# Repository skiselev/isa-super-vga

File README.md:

# isa-super-vga
Trident TVGA9000i based Super VGA board

## Introduction

The ISA Super VGA card is based on the Trident TVGA9000i Super VGA controller IC. It offers excellent compatibility with the original IBM VGA, as well as a good emulation of older CGA, EGA, Hercules and MDA adapters. The ISA Super VGA card was designed to be used with the [Xi 8088 Processor Board](https://github.com/skiselev/xi_8088), but it also works in IBM PC/XT and their clones. It will work in 16-bit ISA slots of AT-compatible computers, but its performance will be inferior to 16-bit VGA cards.

Note: PCB Version 1.0 requires a rework for compatibility with the original IBM PC and IBM XT computers, please see the Errata section below. This errata was fixed in the PCB Version 1.1

## Specifications

* Supports 256 KiB or 512 KiB video memory using two or four 256 Kbit x 4 DRAM ICs.
* 8088-friendly VGA BIOS.
* Only 6 ICs (SVGA IC, BIOS, four DRAM chips), some capacitors, resistors and inductors.

## Hardware Documentation

### Schematic and PCB Layout

[Schematic - Version 1.1](KiCad/ISA_SVGA-Schematic-1.1.pdf)

[PCB Layout - Version 1.1](KiCad/ISA_SVGA-Board-1.1.pdf)

### Bill of Materials

Component Type     | Reference | Description                                               | Quantity | Possible sources and notes
------------------ | --------- | --------------------------------------------------------- | -------- | --------------------------
PCB                |           | ISA Super VGA PCB                                         | 1        | Refer to the [RetroBrew Computers Board Inventory page](https://retrobrewcomputers.org/doku.php?id=boardinventory) for ordering information, or order from a PCB manufacturer of your choice using provided Gerber or KiCad files. Here is [OSH Park project link](https://oshpark.com/shared_projects/M9jRwsu1).
Integrated Circuit | U1        | Trident TVGA9000i-3                                       | 1        | Utsource or other component dealers. Other TVGA9000i versions can be used (e.g. TVGA9000i-1)
Integrated Circuit | U2        | 27C256 UV erasable EPROM or OTP ROM                       | 1        | Unicorn Electronics, Jameco, Mouser (OTP ROM)
Integrated Circuit | U3 - U6   | Micron MT4C4256, Motorola MCM514256, or similar 256 Kbit x 4 DRAM, 70ns or less | 2 or 4 | Unicorn Electronics. Install 4 for the total memory of 512 KiB or two for 256 KiB.
Capacitor          | C1 - C12  | 0.1 uF ceramic, 5.08 mm pitch                             | 12       | Mouser 810-FG28X7R1H104KNT0 
Capacitor          | C13 - C16 | 10 uF, 16V, multilayer ceramic or tantalum, 5.08 mm pitch | 4        | Mouser 810-FG26X7R1E106KRT0 
Capacitor          | C17       | 1 nF ceramic, 5.08 mm pitch                               | 1        | Mouser 810-FG28C0G2A102JNT6
Capacitor          | C18       | 470 pF ceramic, 5.08 mm pitch                             | 1        | Mouser 810-FG28C0G1H471JNT0 
Capacitor          | C19       | 100 pF ceramic, 5.08 mm pitch                             | 1        | Mouser 810-FG28C0G1H101JNT0 
Capacitor          | C20 - C27 | 47 pF ceramic, 5.08 mm pitch                              | 8        | Mouser 810-FG28C0G1H470JNT0
Resistor           | R1 - R8   | 4.7 k, 1/4 W                                              | 8        | Mouser 291-4.7K-RC
Resistor           | R9        | 1 k, 1/4 W                                                | 1        | Mouser 291-1K-RC
Resistor           | R10 - R13 | 150 Ohm, 1/4 W                                            | 4        | Mouser 291-150-RC
Resistor           | R14       | 100 Ohm, 1/4 W                                            | 1        | Mouser 291-100-RC
Resistor           | R15, R16  | 33 Ohm, 1/4 W                                             | 2        | Mouser 291-33-RC
Connector          | P1        | DE15F, right angle PCB mount                              | 1        | Mouser 806-K66X-E15S-NJVESA, 571-1-1734344-1 (blue color), 806-K66X-E15S-NJ30
Connector          | JP1       | 2 pin header                                              | 1        | Mouser 649-68002-102HLF
Inductor           | L1, L3    | 5.7 uH                                                    | 2        | Mouser 542-78F5R6J-RC
Inductor           | L2        | 2.7 uH                                                    | 1        | Mouser 542-78F2R7-RC
Filter             | FB1 - FB6 | EMI Filter Bead                                           | 6        | Mouser 623-2743001112LF
Crystal            | X1        | 40 MHz                                                    | 1        | Mouser 815-ABL-40-B2
Crystal Insulator  | X1        | Bivar CI-192-028-SR                                       | 1        | Mouser 749-CI-192-028-SR, optional, to prevent crystal from shortcircuiting the traces underneath it.
IC Socket          | U2        | 28 pin 600 mil (wide) DIP socket                          | 1        | Mouser 517-4828-6000-CP
IC Socket          | U3 - U6   | 20 pin 300 mil (narrow) DIP socket                        | 4        | Mouser 517-4820-3000-CP
Bracket            |           | ISA card bracket - Keystone 9200-1                        | 1        | Mouser 534-9200-1, or a [3D printed bracket](https://www.thingiverse.com/thing:6473572)

### Construction Notes

#### Display Type Detection

* TVGA9000i VGA controller uses VGA connector pin 12 as **MONITOR** signal to detect the of type of the display. Older, pre-[DDC](https://en.wikipedia.org/wiki/Display_Data_Channel) displays made approximately until 1995, have that signal either unconnected - for color monitors, or grounded - for monochrome monitors. Newer displays use that signal as the DDC/SDA signal. Unfortunately, it can result in TVGA9000i incorrectly detecting the monitor as monochrome. If you're not planning to use monochrome monitor, you can skip FB6 and C17 components. In this case R6 will be pulling the MONITOR signal up, and TVGA9000i will detect the display as a color one.

## Changes

### Version 1.1

* Fix ALE errata. ALE signal is now connected to 5V
* Slightly move VGA DE-9F connector (about 1.27 mm up and 0.8 mm back) to better comply with ISA card size and bracket placement specifications

### Version 1.0

* Minor board modifications around JP1

## Errata

### Version 1.1
* C17 is incorrectly marked as 1 uF on the silkscreen. The correct value is 1 nF, as shown in the BoM. Also see **Display Type Detection** note above.

### Version 1.0

* The original IBM PC, the original IBM XT, and XT clones that closely follow IBM XT schematic do not implement the ALE signal properly. In these computers the ALE signal occasionally activated during DMA cycles, for example during memory refresh, while the address on the address bus is invalid. This confuses the Trident TVGA controller. The following rework is required to make ISA Super VGA work in these computers: The TVGA9000 ALE signal needs to be disconnected from the ISA ALE signal, and connected to the 5V power signal. The photo below shows such modification (photo credit: [keropi](https://forum.vcfed.org/index.php?members/keropi.23086/) at [VCFed forum](https://forum.vcfed.org/index.php)).

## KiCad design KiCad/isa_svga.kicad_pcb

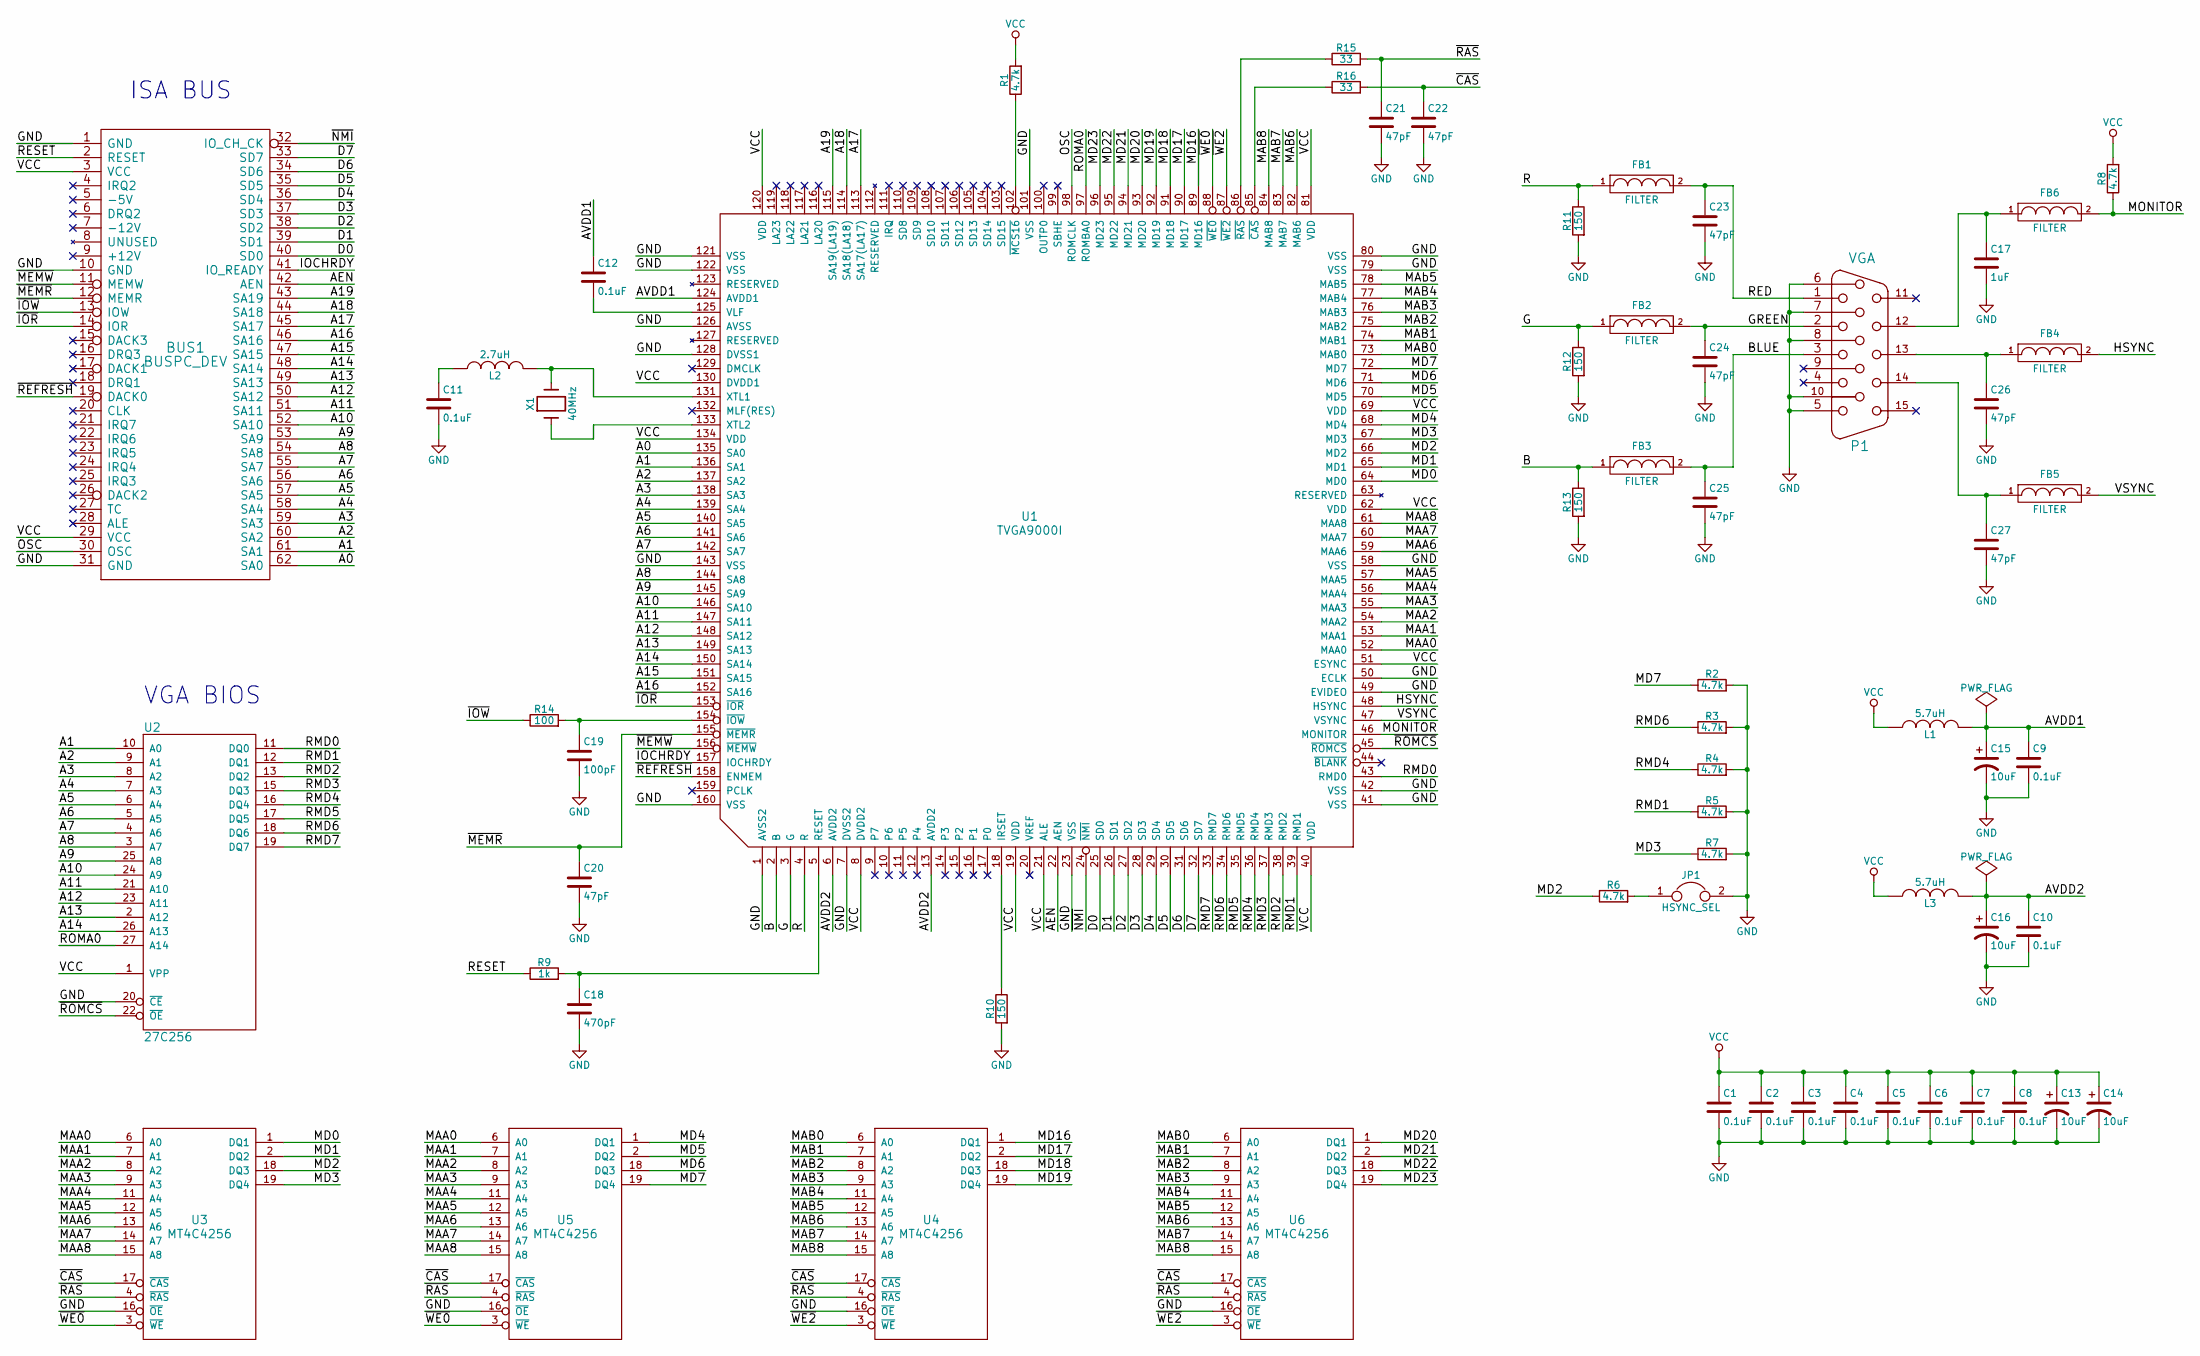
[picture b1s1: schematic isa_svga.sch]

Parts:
BUS1: BUSPC_DEV; Conn_Edge_ISA8
C1, C2, C3, C4, C5, C6, C7, C8, C9, C10, C11, C12: 0.1uF; Cap_Cer_508
C13, C14, C15, C16: 10uF; Cap_Tant_508
C17: 1uF; Cap_Cer_508
C18: 470pF; Cap_Cer_508
C19: 100pF; Cap_Cer_508
C20, C21, C22, C23, C24, C25, C26, C27: 47pF; Cap_Cer_508
FB1, FB2, FB3, FB4, FB5, FB6: FILTER; Res_1016
JP1: HSYNC_SEL; Conn_Pin_Header_2x1_2.54mm_NoKey
L1, L3: 5.7uH; Res_1016
L2: 2.7uH; Res_1016
P1: VGA; Conn_Dsub_DE15F
R1, R2, R3, R4, R5, R6, R7, R8: 4.7k; Res_762
R9: 1k; Res_762
R10, R11, R12, R13: 150; Res_762
R14: 100; Res_762
R15, R16: 33; Res_762
U1: TVGA9000I; IC_PQFP-160
U2: 27C256; IC_DIP28_600
U3, U4, U5, U6: MT4C4256; IC_DIP20_300
X1: 40MHz; Crystal_HC-49U_Vert

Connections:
/A0: BUS1.62 (SA0), U1.135 (SA0)
/A1: BUS1.61 (SA1), U1.136 (SA1), U2.10 (A0)
/A2: BUS1.60 (SA2), U1.137 (SA2), U2.9 (A1)
/A3: BUS1.59 (SA3), U1.138 (SA3), U2.8 (A2)
/A4: BUS1.58 (SA4), U1.139 (SA4), U2.7 (A3)
/A5: BUS1.57 (SA5), U1.140 (SA5), U2.6 (A4)
/A6: BUS1.56 (SA6), U1.141 (SA6), U2.5 (A5)
/A7: BUS1.55 (SA7), U1.142 (SA7), U2.4 (A6)
/A8: BUS1.54 (SA8), U1.144 (SA8), U2.3 (A7)
/A9: BUS1.53 (SA9), U1.145 (SA9), U2.25 (A8)
/A10: BUS1.52 (SA10), U1.146 (SA10), U2.24 (A9)
/A11: BUS1.51 (SA11), U1.147 (SA11), U2.21 (A10)
/A12: BUS1.50 (SA12), U1.148 (SA12), U2.23 (A11)
/A13: BUS1.49 (SA13), U1.149 (SA13), U2.2 (A12)
/A14: BUS1.48 (SA14), U1.150 (SA14), U2.26 (A13)
/A15: BUS1.47 (SA15), U1.151 (SA15)
/A16: BUS1.46 (SA16), U1.152 (SA16)
/A17: BUS1.45 (SA17), U1.113 (SA17(LA17))
/A18: BUS1.44 (SA18), U1.114 (SA18(LA18))
/A19: BUS1.43 (SA19), U1.115 (SA19(LA19))
/AEN: BUS1.42 (AEN), U1.22 (AEN)
/AVDD1: C9.1, C12.1, C15.1, L1.2, U1.124 (AVDD1)
/AVDD2: C10.1, C16.1, L3.2, U1.6 (AVDD2), U1.13 (AVDD2)
/B: FB3.1, R13.1, U1.2 (B)
/BLUE: C25.1, FB3.2, P1.3
/D0: BUS1.40 (SD0), U1.25 (SD0)
/D1: BUS1.39 (SD1), U1.26 (SD1)
/D2: BUS1.38 (SD2), U1.27 (SD2)
/D3: BUS1.37 (SD3), U1.28 (SD3)
/D4: BUS1.36 (SD4), U1.29 (SD4)
/D5: BUS1.35 (SD5), U1.30 (SD5)
/D6: BUS1.34 (SD6), U1.31 (SD6)
/D7: BUS1.33 (SD7), U1.32 (SD7)
/G: FB2.1, R12.1, U1.3 (G)
/GREEN: C24.1, FB2.2, P1.2
/HSYNC: FB4.2, U1.48 (HSYNC)
/IOCHRDY: BUS1.41 (IO_READY), U1.157 (IOCHRDY)
/MAA0: U1.52 (MAA0), U3.6 (A0), U5.6 (A0)
/MAA1: U1.53 (MAA1), U3.7 (A1), U5.7 (A1)
/MAA2: U1.54 (MAA2), U3.8 (A2), U5.8 (A2)
/MAA3: U1.55 (MAA3), U3.9 (A3), U5.9 (A3)
/MAA4: U1.56 (MAA4), U3.11 (A4), U5.11 (A4)
/MAA5: U1.57 (MAA5), U3.12 (A5), U5.12 (A5)
/MAA6: U1.59 (MAA6), U3.13 (A6), U5.13 (A6)
/MAA7: U1.60 (MAA7), U3.14 (A7), U5.14 (A7)
/MAA8: U1.61 (MAA8), U3.15 (A8), U5.15 (A8)
/MAB0: U1.73 (MAB0), U4.6 (A0), U6.6 (A0)
/MAB1: U1.74 (MAB1), U4.7 (A1), U6.7 (A1)
/MAB2: U1.75 (MAB2), U4.8 (A2), U6.8 (A2)
/MAB3: U1.76 (MAB3), U4.9 (A3), U6.9 (A3)
/MAB4: U1.77 (MAB4), U4.11 (A4), U6.11 (A4)
/MAB5: U1.78 (MAB5), U4.12 (A5), U6.12 (A5)
/MAB6: U1.82 (MAB6), U4.13 (A6), U6.13 (A6)
/MAB7: U1.83 (MAB7), U4.14 (A7), U6.14 (A7)
/MAB8: U1.84 (MAB8), U4.15 (A8), U6.15 (A8)
/MD0: U1.64 (MD0), U3.1 (DQ1)
/MD1: U1.65 (MD1), U3.2 (DQ2)
/MD2: R6.1, U1.66 (MD2), U3.18 (DQ3)
/MD3: R7.1, U1.67 (MD3), U3.19 (DQ4)
/MD4: U1.68 (MD4), U5.1 (DQ1)
/MD5: U1.70 (MD5), U5.2 (DQ2)
/MD6: U1.71 (MD6), U5.18 (DQ3)
/MD7: R2.1, U1.72 (MD7), U5.19 (DQ4)
/MD16: U1.89 (MD16), U4.1 (DQ1)
/MD17: U1.90 (MD17), U4.2 (DQ2)
/MD18: U1.91 (MD18), U4.18 (DQ3)
/MD19: U1.92 (MD19), U4.19 (DQ4)
/MD20: U1.93 (MD20), U6.1 (DQ1)
/MD21: U1.94 (MD21), U6.2 (DQ2)
/MD22: U1.95 (MD22), U6.18 (DQ3)
/MD23: U1.96 (MD23), U6.19 (DQ4)
/MONITOR: FB6.2, R8.1, U1.46 (MONITOR)
/OSC: BUS1.30 (OSC), U1.98 (ROMCLK)
/R: FB1.1, R11.1, U1.4 (R)
/RED: C23.1, FB1.2, P1.1
/RESET: BUS1.2 (RESET), R9.1
/RMD0: U1.43 (RMD0), U2.11 (DQ0)
/RMD1: R5.1, U1.39 (RMD1), U2.12 (DQ1)
/RMD2: U1.38 (RMD2), U2.13 (DQ2)
/RMD3: U1.37 (RMD3), U2.15 (DQ3)
/RMD4: R4.1, U1.36 (RMD4), U2.16 (DQ4)
/RMD5: U1.35 (RMD5), U2.17 (DQ5)
/RMD6: R3.1, U1.34 (RMD6), U2.18 (DQ6)
/RMD7: U1.33 (RMD7), U2.19 (DQ7)
/ROMA0: U1.97 (ROMBA0), U2.27 (A14)
/VSYNC: FB5.2, U1.47 (VSYNC)
/~CAS: C22.1, R16.2, U3.17 (~CAS), U4.17 (~CAS), U5.17 (~CAS), U6.17 (~CAS)
/~IOR: BUS1.14 (IOR), U1.153 (~IOR)
/~IOW: BUS1.13 (IOW), R14.1
/~MEMR: BUS1.12 (MEMR), C20.1, U1.155 (~MEMR)
/~MEMW: BUS1.11 (MEMW), U1.156 (~MEMW)
/~NMI: BUS1.32 (IO_CH_CK), U1.24 (~NMI)
/~RAS: C21.1, R15.2, U3.4 (~RAS), U4.4 (~RAS), U5.4 (~RAS), U6.4 (~RAS)
/~REFRESH: BUS1.19 (DACK0), U1.158 (ENMEM)
/~ROMCS: U1.45 (~ROMCS), U2.22 (~OE)
/~WE0: U1.88 (~WE0), U3.3 (~WE), U5.3 (~WE)
/~WE2: U1.87 (~WE2), U4.3 (~WE), U6.3 (~WE)
GND: BUS1.1 (GND), BUS1.10 (GND), BUS1.31 (GND), C1.2, C2.2, C3.2, C4.2, C5.2, C6.2, C7.2, C8.2, C9.2, C10.2, C11.2, C13.2, C14.2, C15.2, C16.2, C17.2, C18.2, C19.2, C20.2, C21.2, C22.2, C23.2, C24.2, C25.2, C26.2, C27.2, JP1.2, P1.5, P1.6, P1.7, P1.8, P1.10, R2.2, R3.2, R4.2, R5.2, R7.2, R10.2, R11.2, R12.2, R13.2, U1.1 (AVSS2), U1.7 (DVSS2), U1.23 (VSS), U1.41 (VSS), U1.42 (VSS), U1.49 (EVIDEO), U1.50 (ECLK), U1.58 (VSS), U1.79 (VSS), U1.80 (VSS), U1.101 (VSS), U1.121 (VSS), U1.122 (VSS), U1.126 (AVSS), U1.128 (DVSS1), U1.143 (VSS), U1.160 (VSS), U2.14 (GND), U2.20 (~CE), U3.16 (~OE), U3.20 (GND), U4.16 (~OE), U4.20 (GND), U5.16 (~OE), U5.20 (GND), U6.16 (~OE), U6.20 (GND)
unnamed: C11.1, L2.1
unnamed: C12.2, U1.125 (VLF)
unnamed: C17.1, FB6.1, P1.12
unnamed: C18.1, R9.2, U1.5 (RESET)
unnamed: C19.1, R14.2, U1.154 (~IOW)
unnamed: C26.1, FB4.1, P1.13
unnamed: C27.1, FB5.1, P1.14
unnamed: JP1.1, R6.2
unnamed: L2.2, U1.131 (XTL1), X1.2
unnamed: R1.1, U1.102 (~MCS16)
unnamed: R10.1, U1.18 (IRSET)
unnamed: R15.1, U1.86 (~RAS)
unnamed: R16.1, U1.85 (~CAS)
unnamed: U1.133 (XTL2), X1.1
VCC: BUS1.3 (VCC), BUS1.29 (VCC), C1.1, C2.1, C3.1, C4.1, C5.1, C6.1, C7.1, C8.1, C13.1, C14.1, L1.1, L3.1, R1.2, R8.2, U1.8 (DVDD2), U1.19 (VDD), U1.21 (ALE), U1.40 (VDD), U1.51 (ESYNC), U1.62 (VDD), U1.69 (VDD), U1.81 (VDD), U1.120 (VDD), U1.130 (DVDD1), U1.134 (VDD), U2.1 (VPP), U2.28 (VCC), U3.10 (VCC), U4.10 (VCC), U5.10 (VCC), U6.10 (VCC)

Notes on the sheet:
VGA BIOS
ISA BUS

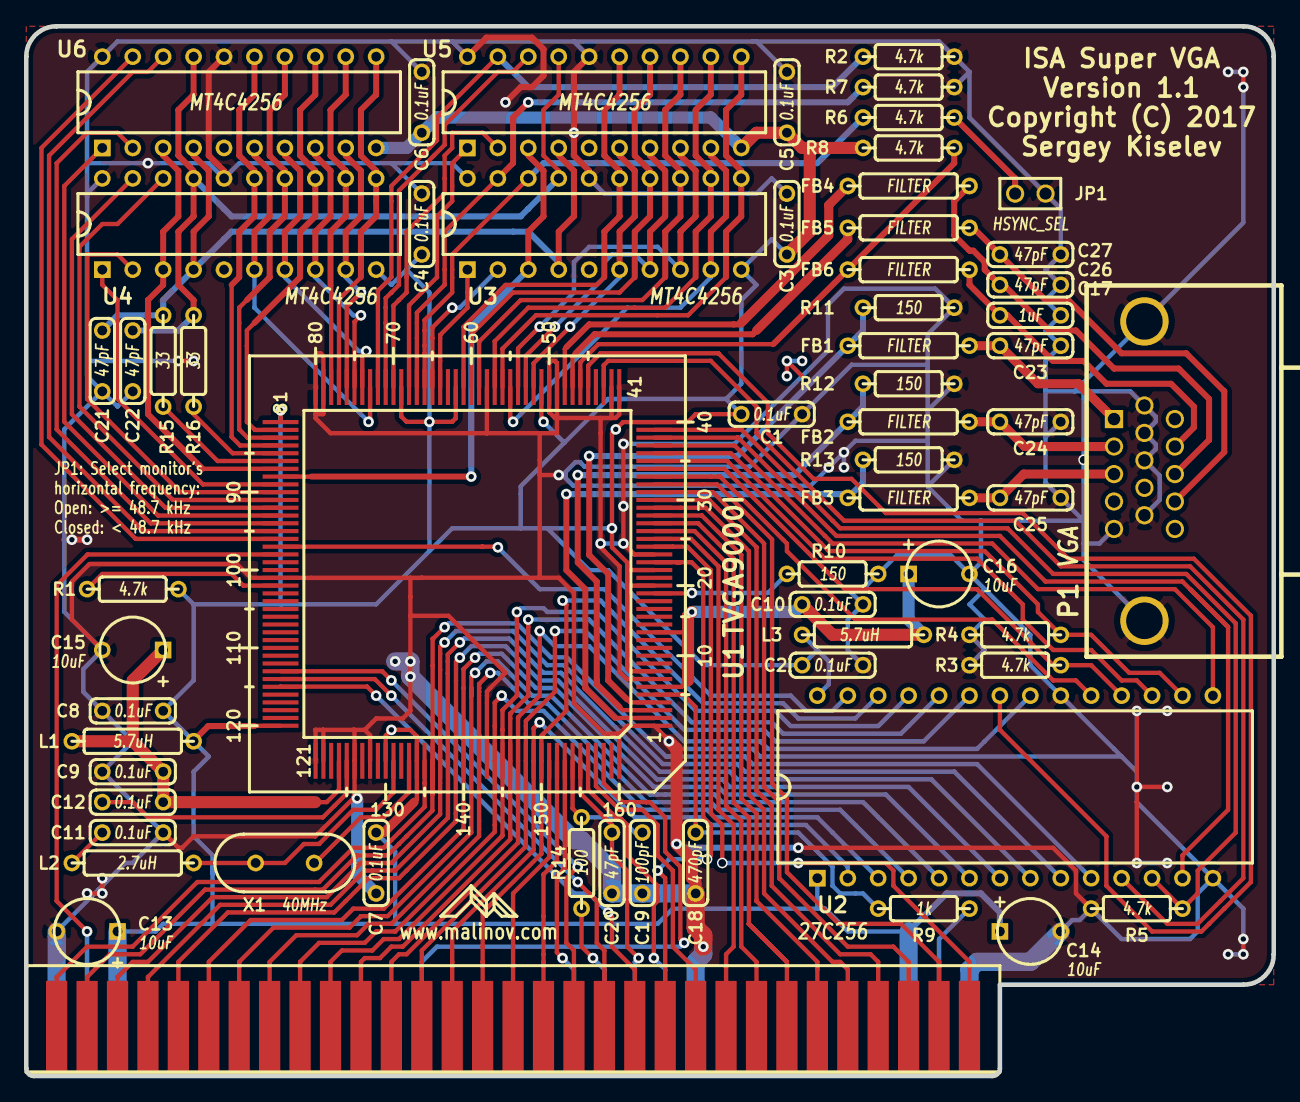
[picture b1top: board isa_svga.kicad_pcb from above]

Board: 2 copper layers, 104.1 x 87.6 mm, 62 parts (0 on the bottom side), 113 nets.

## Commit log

2023-10-31 Add v0.8 files
2023-10-31 Add v0.9 files
2023-10-31 Add v1.0 files
2023-10-31 Add v1.0 board pdf
2023-10-31 Add v1.1 files
2023-10-31 Add README content
2023-10-31 Add Changes and Errata
2023-10-31 Add schematic and PCB links, add notes about MONITOR signal
2024-02-07 Add link to a 3D printed bracket
2024-11-19 Added Russified firmware. Russian fonts are loaded into the video card firmware.
2025-01-10 README: Replace TDK FK series capacitors with FG series
    Replace TDK FK series capacitors that are not recommended for new designs, with newer FG series capacitors
2025-01-27 README: BoM: Add an insulator for the crystal

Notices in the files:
KiCad/isa_svga.kicad_pcb:
Copyright (C) 2017
